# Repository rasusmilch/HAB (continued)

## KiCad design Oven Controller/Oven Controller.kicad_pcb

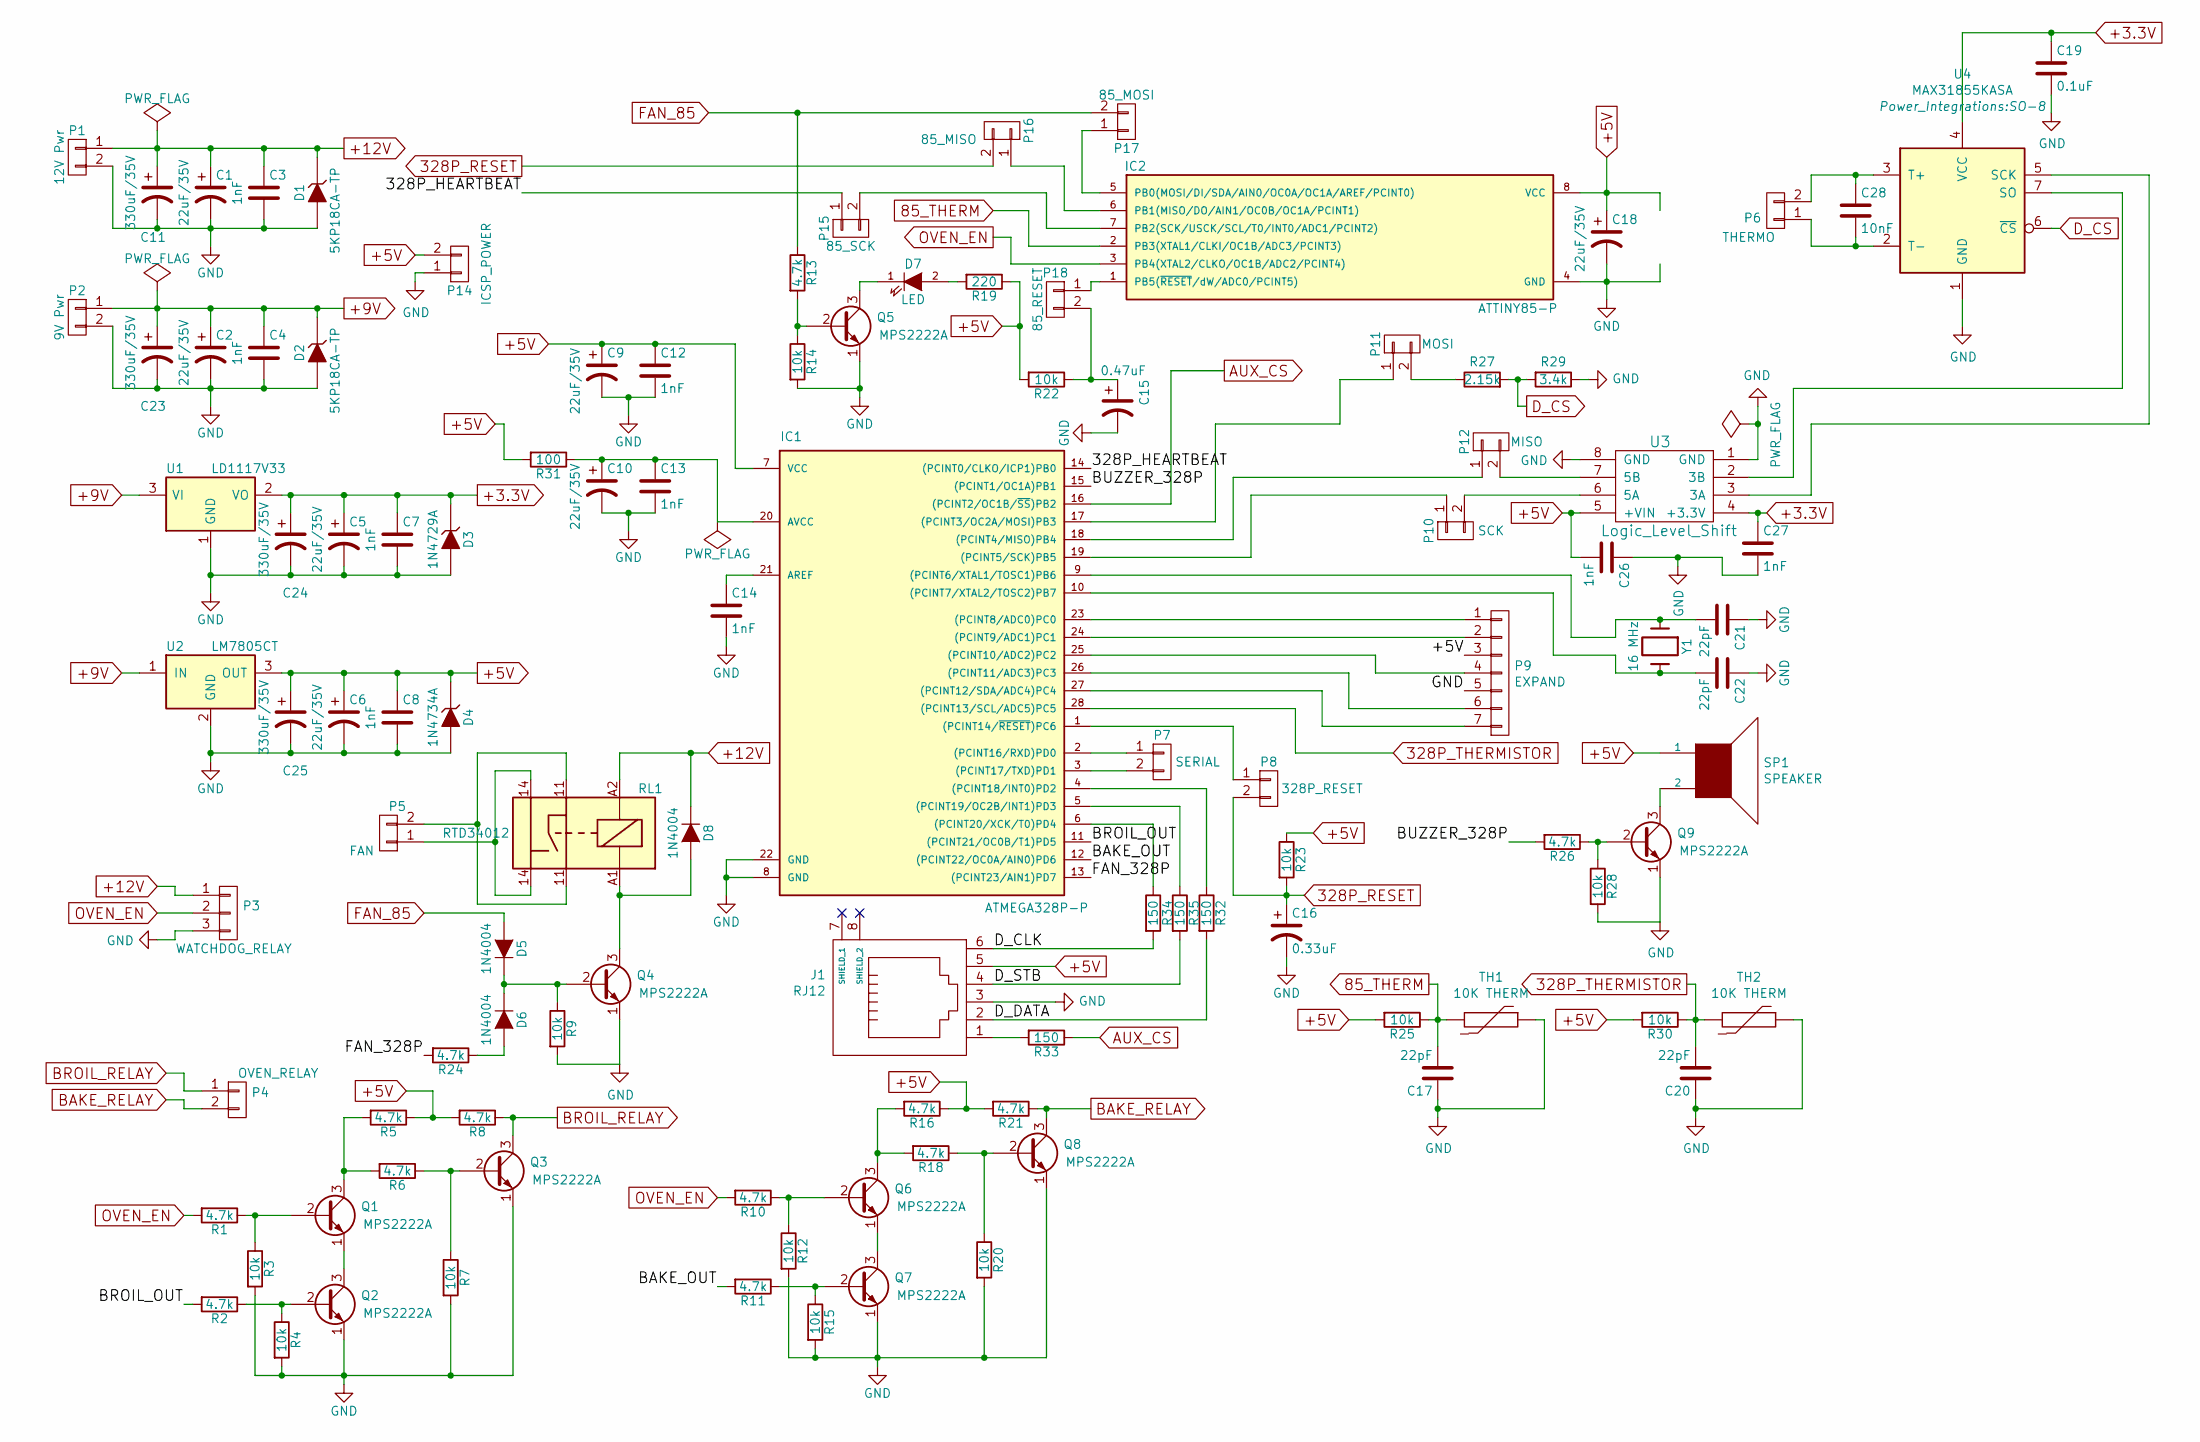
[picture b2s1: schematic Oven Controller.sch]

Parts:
C1, C2, C5, C6, C9, C10, C18: 22uF/35V; C_Radial_D8_L11.5_P3.5
C3, C4, C7, C8, C12, C13, C14, C26, C27: 1nF; C_Disc_D5_P7
C11, C23, C24, C25: 330uF/35V; C_Radial_D8_L11.5_P3.5
C15: 0.47uF; C_Radial_D5_L6_P2.5
C16: 0.33uF; C_Radial_D5_L11_P2.5
C17, C20, C21, C22: 22pF; C_Disc_D3_P2.5
C19: 0.1uF; C_Disc_D5_P7
C28: 10nF; C_Disc_D5_P7
D1, D2: 5KP18CA-TP; R6
D3: 1N4729A; Diode_DO-35_SOD27_Horizontal_RM10
D4: 1N4734A; Diode_DO-35_SOD27_Horizontal_RM10
D5, D6, D8: 1N4004; Diode_DO-35_SOD27_Horizontal_RM10
D7: LED; LED-5MM
IC1: ATMEGA328P-P; DIP-28_W7.62mm_LongPads
IC2: ATTINY85-P; DIP-8_W7.62mm_LongPads
J1: RJ12; RJ12_JACK
P1: 12V Pwr; 2_Pole_Screw_Connector
P2: 9V Pwr; 2_Pole_Screw_Connector
P3: WATCHDOG_RELAY; 3_Pole_Screw_Connector
P4: OVEN_RELAY; 2_Pole_Screw_Connector
P5: FAN; 2_Pole_Screw_Connector
P6: THERMO; 2_Pole_Screw_Connector
P7: SERIAL; Pin_Header_Straight_1x02
P8: 328P_RESET; Pin_Header_Straight_1x02
P9: EXPAND; Pin_Header_Straight_1x07
P10: SCK; Pin_Header_Straight_1x02
P11: MOSI; Pin_Header_Straight_1x02
P12: MISO; Pin_Header_Straight_1x02
P14: ICSP_POWER; Pin_Header_Straight_1x02
P15: 85_SCK; Pin_Header_Straight_1x02
P16: 85_MISO; Pin_Header_Straight_1x02
P17: 85_MOSI; Pin_Header_Straight_1x02
P18: 85_RESET; Pin_Header_Straight_1x02
Q1, Q2, Q3, Q4, Q5, Q6, Q7, Q8, Q9: MPS2222A; TO-92_Inline_Narrow_Oval
R1, R2, R5, R6, R8, R10, R11, R13, R16, R18, R21, R24, R26: 4.7k; Resistor_Horizontal_RM10mm
R3, R4, R7, R9, R12, R14, R15, R20, R22, R23, R25, R28, R30: 10k; Resistor_Horizontal_RM10mm
R19: 220; Resistor_Horizontal_RM10mm
R27: 2.15k; Resistor_Horizontal_RM10mm
R29: 3.4k; Resistor_Horizontal_RM10mm
R31: 100; Resistor_Horizontal_RM10mm
R32, R33, R34, R35: 150; Resistor_Horizontal_RM10mm
RL1: RTD34012; Relay_SPST_RTD34012
SP1: SPEAKER; Buzzer_12x9.5RM7.6
TH1, TH2: 10K THERM; R4
U1: LD1117V33; TO-220
U2: LM7805CT; TO-220
U3: Logic_Level_Shift; Logic_Level_Shifter
U4: MAX31855KASA; SO-8
Y1: 16 MHz; HC-49V

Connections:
85_THERM: C17.2, IC2.2 (PB3(XTAL1/CLKI/OC1B/ADC3/PCINT3)), R25.1, TH1.2
328P_RESET: C16.1, P8.2, P16.2, R23.2
328P_THERMISTOR: C20.2, IC1.28 ((PCINT13/SCL/ADC5)PC5), R30.1, TH2.2
+3.3V: C5.1, C7.1, C19.1, C24.1, C27.1, D3.1 (K), U1.2 (VO), U3.4 (+3.3V), U4.4 (VCC)
+5V: C6.1, C8.1, C9.1, C12.1, C18.1, C25.1, C26.2, D4.1 (K), IC1.7 (VCC), IC2.8 (VCC), J1.5, P9.3, P14.2, R5.1, R8.2, R16.1, R19.1, R21.2, R22.2, R23.1, R25.2, R30.2, R31.2, SP1.1, U2.3 (OUT), U3.5 (+VIN)
+9V: C2.1, C4.1, C23.1, D2.1 (K), P2.1, U1.3 (VI), U2.1 (IN)
+12V: C1.1, C3.1, C11.1, D1.1 (K), D8.1 (K), P1.1, P3.1, RL1.A2
/328P_HEARTBEAT: IC1.14 ((PCINT0/CLKO/ICP1)PB0), P15.1
/BAKE_OUT: IC1.12 ((PCINT22/OC0A/AIN0)PD6), R11.2
/BROIL_OUT: IC1.11 ((PCINT21/OC0B/T1)PD5), R2.2
/BUZZER_328P: IC1.15 ((PCINT1/OC1A)PB1), R26.2
/D_CLK: J1.6, R34.2
/D_DATA: J1.2, R32.2
/D_STB: J1.4, R35.2
/FAN_328P: IC1.13 ((PCINT23/AIN1)PD7), R24.2
AUX_CS: IC1.16 ((PCINT2/OC1B/~SS~)PB2), R33.1
BAKE_RELAY: P4.2, Q8.3 (C), R21.1
BROIL_RELAY: P4.1, Q3.3 (C), R8.1
D_CS: R27.2, R29.2, U4.6 (~CS~)
FAN_85: D5.2 (A), P17.2, R13.1
GND: C1.2, C2.2, C3.2, C4.2, C5.2, C6.2, C7.2, C8.2, C9.2, C10.2, C11.2, C12.2, C13.2, C14.2, C15.2, C16.2, C17.1, C18.2, C19.2, C20.1, C21.1, C22.1, C23.2, C24.2, C25.2, C26.1, C27.2, D1.2 (A), D2.2 (A), D3.2 (A), D4.2 (A), IC1.8 (GND), IC1.22 (GND), IC2.4 (GND), J1.3, P1.2, P2.2, P3.3, P9.5, P14.1, Q2.1 (E), Q3.1 (E), Q4.1 (E), Q5.1 (E), Q7.1 (E), Q8.1 (E), Q9.1 (E), R3.2, R4.2, R7.2, R9.2, R12.2, R14.2, R15.2, R20.2, R28.2, R29.1, TH1.1, TH2.1, U1.1 (GND), U2.2 (GND), U3.1 (GND), U3.8 (GND), U4.1 (GND)
unnamed: C10.1, C13.1, IC1.20 (AVCC), R31.1
unnamed: C14.1, IC1.21 (AREF)
unnamed: C15.1, P18.2, R22.1
unnamed: C21.2, IC1.9 ((PCINT6/XTAL1/TOSC1)PB6), Y1.1
unnamed: C22.2, IC1.10 ((PCINT7/XTAL2/TOSC2)PB7), Y1.2
unnamed: C28.1, P6.2, U4.3 (T+)
unnamed: C28.2, P6.1, U4.2 (T-)
unnamed: D5.1 (K), D6.1 (K), Q4.2 (B), R9.1
unnamed: D6.2 (A), R24.1
unnamed: D7.1 (K), Q5.3 (C)
unnamed: D7.2 (A), R19.2
unnamed: D8.2 (A), Q4.3 (C), RL1.A1
unnamed: IC1.1 ((PCINT14/~RESET~)PC6), P8.1
unnamed: IC1.2 ((PCINT16/RXD)PD0), P7.1
unnamed: IC1.3 ((PCINT17/TXD)PD1), P7.2
unnamed: IC1.4 ((PCINT18/INT0)PD2), R32.1
unnamed: IC1.5 ((PCINT19/OC2B/INT1)PD3), R35.1
unnamed: IC1.6 ((PCINT20/XCK/T0)PD4), R34.1
unnamed: IC1.17 ((PCINT3/OC2A/MOSI)PB3), P11.1
unnamed: IC1.18 ((PCINT4/MISO)PB4), P12.1
unnamed: IC1.19 ((PCINT5/SCK)PB5), P10.1
unnamed: IC1.23 ((PCINT8/ADC0)PC0), P9.1
unnamed: IC1.24 ((PCINT9/ADC1)PC1), P9.2
unnamed: IC1.25 ((PCINT10/ADC2)PC2), P9.4
unnamed: IC1.26 ((PCINT11/ADC3)PC3), P9.6
unnamed: IC1.27 ((PCINT12/SDA/ADC4)PC4), P9.7
unnamed: IC2.1 (PB5(~RESET~/dW/ADC0/PCINT5)), P18.1
unnamed: IC2.5 (PB0(MOSI/DI/SDA/AIN0/OC0A/OC1A/AREF/PCI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), P17.1
unnamed: IC2.6 (PB1(MISO/DO/AIN1/OC0B/OC1A/PCINT1)), P16.1
unnamed: IC2.7 (PB2(SCK/USCK/SCL/T0/INT0/ADC1/PCINT2)), P15.2
unnamed: J1.1, R33.2
unnamed: P5.1, RL1.14
unnamed: P5.2, RL1.11
unnamed: P10.2, U3.6 (5A)
unnamed: P11.2, R27.1
unnamed: P12.2, U3.7 (5B)
unnamed: Q1.1 (E), Q2.3 (C)
unnamed: Q1.2 (B), R1.1, R3.1
unnamed: Q1.3 (C), R5.2, R6.2
unnamed: Q2.2 (B), R2.1, R4.1
unnamed: Q3.2 (B), R6.1, R7.1
unnamed: Q5.2 (B), R13.2, R14.1
unnamed: Q6.1 (E), Q7.3 (C)
unnamed: Q6.2 (B), R10.1, R12.1
unnamed: Q6.3 (C), R16.2, R18.2
unnamed: Q7.2 (B), R11.1, R15.1
unnamed: Q8.2 (B), R18.1, R20.1
unnamed: Q9.2 (B), R26.1, R28.1
unnamed: Q9.3 (C), SP1.2
unnamed: U3.2 (3B), U4.7 (SO)
unnamed: U3.3 (3A), U4.5 (SCK)
OVEN_EN: IC2.3 (PB4(XTAL2/CLKO/OC1B/ADC2/PCINT4)), P3.2, R1.2, R10.2

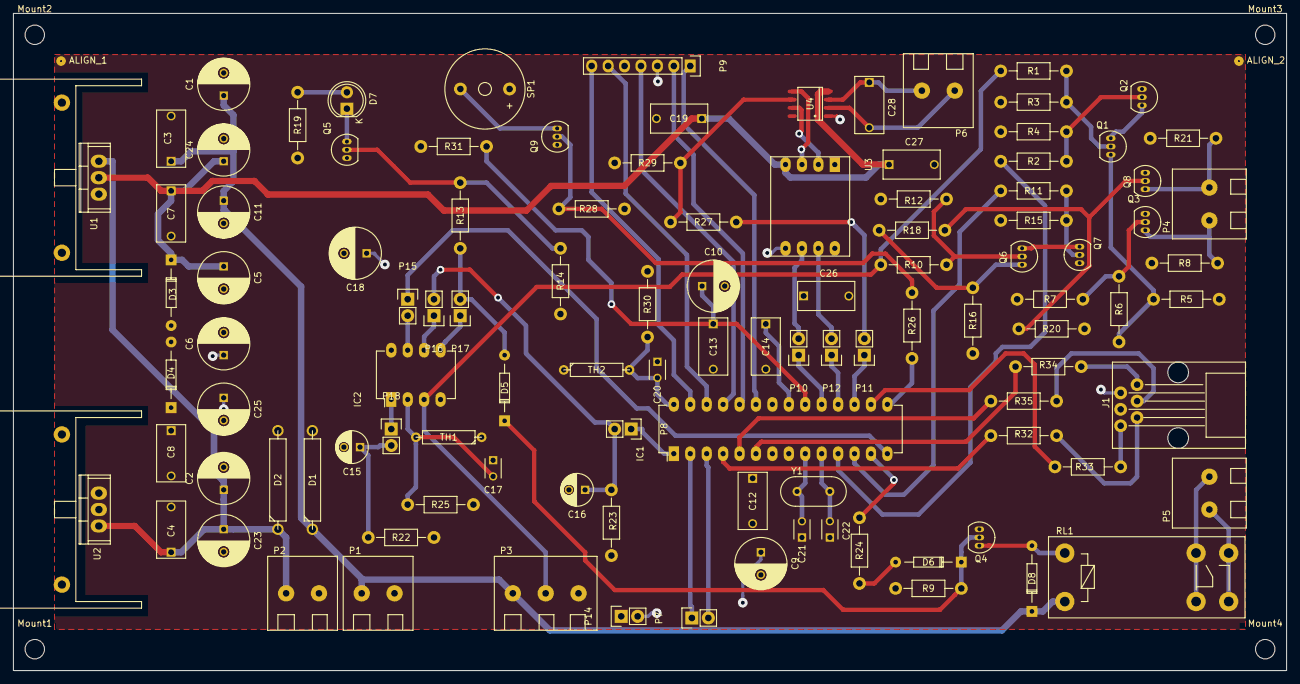
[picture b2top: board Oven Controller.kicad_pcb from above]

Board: 2 copper layers, 196.9 x 101.6 mm, 116 parts (0 on the bottom side), 73 nets.

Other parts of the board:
ALIGN_1, ALIGN_2: Measurement_Point_Round-TH_Small
HS_U1, HS_U2: TO220 Silver Heatsink; TO220_Silver_Heatsink
Mount1, Mount2, Mount3, Mount4: MountingHole_3mm

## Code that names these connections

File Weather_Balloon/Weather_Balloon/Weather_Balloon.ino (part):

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// CO2 analog pin
#define CO2_PIN A3

// Piezo pin
#define PIEZO_PIN   A2

#define GREEN_LED     22
#define YELLOW_LED  23
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
    // If the current pin state is low, and previous it was high, we have
    // a falling edge.
    if ((current_state_j & (1<<PJ1)) == 0 && (previous_pins_j & (1<<PJ1)) > 0) {
      // Trigger count
      geiger.y_count++;
    }

    if ((current_state_j & (1<<PJ0)) == 0 && (previous_pins_j & (1<<PJ0)) > 0) {
      // Trigger count
      geiger.x_count++;
    }
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
    // If the current pin state is low, and previous it was high, we have
    // a falling edge.
    if ((current_state_k & (1<<PK7)) == 0 && (previous_pins_k & (1<<PK7)) > 0) {
      // Trigger count
      geiger.z_count++;
    }
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
    // If the current pin state is high, and previous it was low, we have
    // a rising edge.
    if ((current_state_e & (1<<PE4)) >= 1 && (previous_pins_e & (1<<PE4)) == 0) {
        button = true;
        button_time = current_time;
        led_status = PINA & (1 << PA0) & (1 << PA1) & (1 << PA2);

        PORTA &= ~(1 << PA0) & ~(1 << PA1) & ~(1 << PA2);
    } else if ((current_state_e & (1 << PE4)) == 0 && ((previous_pins_e & (1 << PE4)) >= 1)) {
        PORTA |= (1 << PA0) | (1 << PA1) | (1 << PA2);

        if ((current_time - button_time) > 1000L && (current_time - button_time) < 5000L) {
            reset_flag = true;
            PORTA |= (1 << PA0) | (1 << PA1) | (1 << PA2);
        } else {
            reset_flag = false;
            PORTA |= (1 << PA0) | (1 << PA1) | (1 << PA2);
        }

    } else {
        PORTA |= (1 << PA0) | (1 << PA1) | (1 << PA2);
    }

    // Store for later.
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    // Enable pin interrupts for Geiger counter on

    // X axis
    // pin 64 (PJ1, PCINT10, TXD3), on PCIE1.
    // Arduino D14 (TX3)

    // Y-axis
    // pin 63 (PJ0, PCINT10, RXD3), on PCIE1.
    // Arduino D15 (RX3)

    // Z-axis
    // pin 63 (PK7, PCINT23, ADC15), on PCIE2.
    // Arduino A15 (ADC15)

    // Set as input for high impedance. However, this will allow
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void piezo_power(bool power) {
    if (power == true) {
        // PIEZO POWER
        DDRJ |= (1 << PJ7);
        PORTJ |= (1 << PJ7);
    } else {
        // PIEZO POWER
        DDRJ &= ~(1 << PJ7);
        PORTJ &= ~(1 << PJ7);
    }
}

void tsl2561_power(bool power) {
    if (power == true) {
        // TSL2561 as output
        DDRJ |= (1 << PJ5);
        // Turn on TSL2561
        PORTJ |= (1 << PJ5);
    } else {
        //Tristate
        DDRJ &= ~(1 << PJ5);
        PORTJ &= ~(1 << PJ5);
    }
}

void ms5607_power(bool power) {
    if (power == true) {
        // As output
        DDRJ |= (1 << PJ6);
        // Turn on
        PORTJ |= (1 << PJ6);
    } else {
        //Tristate
        DDRJ &= ~(1 << PJ6);
        PORTJ &= ~(1 << PJ6);
    }
}

void sht31_power(bool power) {
    if (power == true) {
        DDRJ |= (1 << PJ3);

        // SHT31 reset is inverse of power control. Shorting to ground resets sensor
        // but holds I2C hostage.
        PORTJ &= ~(1 << PJ3);
    } else {
        // Tri state
        DDRJ &= ~(1 << PJ3);
        PORTJ &= ~(1 << PJ3);
    }
}

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void sd_power(bool power) {
    if (power == true) {
        // SD Power
        DDRG |= (1 << PG1);
        PORTG |= (1 << PG1);
    } else {
        // Tristate
        DDRG &= ~(1 << PG1);
        PORTG &= ~(1 << PG1);
    }
}

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void ds18b20_power(bool power) {
    if (power == true) {
        // DS18B20 Power
        DDRE |= (1 << PE2);
        PORTE |= (1 << PE2);
    } else {
        // Tri state
        DDRE &= ~(1 << PE2);
        PORTE &= ~(1 << PE2);
    }
}

void dof_power(bool power) {
    if (power == true) {
        // 9DOF
        DDRA |= (1 << PA7);
        PORTA |= (1 << PA7);
    } else {
        // Tristate
        DDRA &= ~(1 << PA7);
        PORTA &= ~(1 << PA7);
    }
}

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        flash_landing(10);
        piezo_power(true);
        //Serial.begin(115200);
        beep_piezo(1000L, 250L, PIEZO_PIN);
        beep_piezo(2000L, 250L, PIEZO_PIN);
        piezo_power(false);
    }
}
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        reset_flag = false;
        flash_landing(10);
        piezo_power(true);
        beep_piezo(1000, 250, PIEZO_PIN);
        delay(100);
        flash_landing(10);
        beep_piezo(2000, 250, PIEZO_PIN);
        piezo_power(false);
    }

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
        clock.begin();

        beep_piezo(1000, 250, PIEZO_PIN);



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
void flash_landing(uint16_t time) {
    // Flash location landing lights for time ms.
    DDRF |= (1 << PF1);
    PORTF |= (1 << PF1);
    delay(time);
    DDRF &= ~(1 << PF1);
    PORTF &= ~(1 << PF1);

}

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
        piezo_power(true);
        flash_landing(10);
        beep_piezo(1000, 250, PIEZO_PIN);
        flash_landing(250);
        beep_piezo(2000, 500, PIEZO_PIN);
        piezo_power(false);
        led_power(false);

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        EEPROM.put(0, default_config);
        reset_flag = false;
        flash_landing(10);
        beep_piezo(1000, 250, PIEZO_PIN);
        //delay(100);
        flash_landing(10);
        beep_piezo(2000, 250, PIEZO_PIN);
    }

    if (DEBUG == true) {
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
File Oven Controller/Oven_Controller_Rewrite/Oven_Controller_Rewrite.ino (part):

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// PD# = Port D #

// Define a TM1638 display/keypad module
#define TM1638_DATA     5       // PD5. BM11
#define TM1638_STRB     6       // PD6. BM12
#define TM1638_CLK      7       // PD7. BM13

#define BI_COLOR        true

// Display utilizing MAX7219. Not I2C. Partially SPI, where the MAX7221 *IS* fully SPI compatible.
/*
#define MAX_DISP_DATA   8        // PB0. BM14
#define MAX_DISP_CS     9        // PB1. BM15
#define MAX_DISP_CLK    10       // PB2. BM16
*/

// Attempt to use the same clock and data lines.
#define MAX_DISP_DATA   5        // PB0. BM14
#define MAX_DISP_CS     9        // PB1. BM15
#define MAX_DISP_CLK    7       // PB2. BM16


// Creating a thermocouple instance with software SPI on any three
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#define MAXCLK  13              // Port B 5. Bare metal 19. SCK.

// Pin to toggle the external watchdog.
#define WATCHDOG_PIN    14      // A0. Low-level PC0. Bare metal 23.

// Control pins
#define BUZZER_PIN        15    // PC1. A1. BM24
#define FAN_PIN           16    // PC2. A2. BM25
#define BAKE_ELEMENT_PIN  17    // PC3. A3. BM26
#define BROIL_ELEMENT_PIN 18    // PC2. A4. BM27

// Thermistor ADC values
// 54C = 235
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// 70C = 150
// 80C = 110
// adc = 1504.85 - 318.56 * ln(temp)
#define THERMISTOR_PIN      A5  // PC5. BM28

#define DEBOUNCE_TIME     250
#define BUTTON_TEMP_DIFF    10
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
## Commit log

2016-09-10 Beeper working. Magnetometer and 18B20.
2016-09-11 Added accelerometer and non-blocking DS18B20 temperature conversion
2016-09-16 Refactored to use generic Makefile instead of Arduino IDE. Allowing external IDE and more traditional Cpp
2016-09-18 Progress on new sensors, fuel gauge.
2016-09-20 Restructured sensor data. GPS works.
2016-09-20 Calibration of accel, mag and gyro.
2016-09-21 Geiger count ISR and reorganize sensor configs. New sensor found struct.
2016-09-25 Logging packed
2016-09-27 Initial PCB design with throughhole components. Layout not finilized.
2016-09-29 Before manual trace width adjust
2016-10-01 Reorganized folder structure
2016-10-01 Restructured folders to move board level files to board directory.
2016-10-02 Updated PCB board for larger traces and more compact design.
2016-10-11 PID control and beginning of altitude alarm.
2016-10-12 Prototype pre-assembly with debugging enabled
2016-10-13 Launch code finalized.
2016-10-14 Added SDCard CSV dump function and some serial commands. Untested.
2016-10-14 After flight data retrieval
2016-10-15 Investigated serial command read failure on atmega328p. Found nothing. Added pressure calculation to set altitude command.
2016-11-07 Update before move to github
2016-11-07 Early rough draft of the Design Document
2016-11-09 Updated board schematic and layout files to remove title block and page outline for presentation.
2016-11-10 Design document rev 1.0
